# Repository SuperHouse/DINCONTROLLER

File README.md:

DIN-Mount ESP32 Controller with I/O Breakout
=============================================
Copyright 2017-2018 SuperHouse Automation Pty Ltd  www.superhouse.tv  

ESP32 controller board designed to fit into the top part of DIN rail
case H8456.

Includes 8 illuminated buttons for input, and an I/O Breakout header
(12-pin IDC) compatible with other I/O Breakout boards from SuperHouse.

More information is available at:

  http://www.superhouse.tv/dinrelay8

INSTALLATION
------------
The design is saved as an EAGLE project. EAGLE PCB design software is
available from www.cadsoftusa.com free for non-commercial use. To use
this project download it and place the directory containing these files
into the "eagle" directory on your computer. Then open EAGLE and
navigate to the project.

DISTRIBUTION
------------
The specific terms of distribution of this project are governed by the
license referenced below.

LICENSE
-------
Licensed under the TAPR Open Hardware License (www.tapr.org/OHL).
The "license" folder within this repository also contains a copy of
this license in plain text format.

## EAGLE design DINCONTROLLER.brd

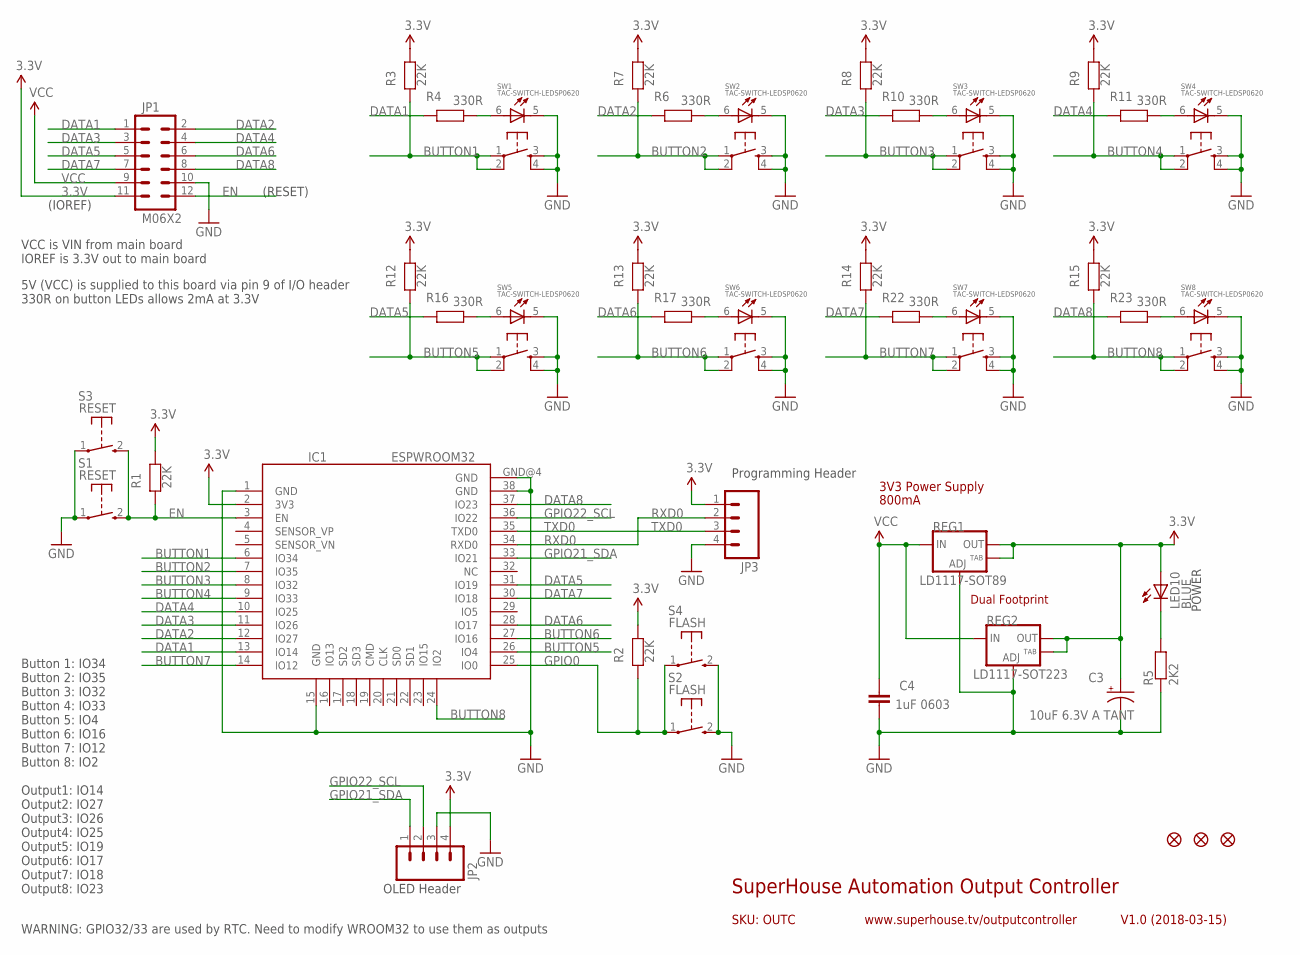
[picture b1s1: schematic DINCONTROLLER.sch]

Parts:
C3: 10uF 6.3V A TANT; EIA3216
C4: 1uF 0603; 0603
FID1, FID2, FID3: FIDUCIAL1X2.5; FIDUCIAL-1X2.5
IC1: ESPWROOM32
JP1: M06X2; 2X6-SHROUDED
JP2, JP3: M04PTH; 1X04
LED10: BLUE; LED3MM
R1, R2, R3, R7, R8, R9, R12, R13, R14, R15: 22K; 0603@2
R4, R6, R10, R11, R16, R17, R22, R23: 330R; 0603@2
R5: 2K2; 0603
REG1: LD1117-SOT89; SOT89
REG2: LD1117-SOT223; SOT223
S1, S3: RESET; TACTILE_SWITCH_SMD_2PIN_TINY
S2, S4: FLASH; TACTILE_SWITCH_SMD_2PIN_TINY
SW1, SW2, SW3, SW4, SW5, SW6, SW7, SW8: TAC-SWITCH-LEDSP0620; TACTILE-PTH-SP0620

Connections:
3.3V: C3.A (+), IC1.2 (3V3), JP1.11, JP2.4, JP3.1, LED10.A, R1.1, R2.1, R3.1, R7.1, R8.1, R9.1, R12.1, R13.1, R14.1, R15.1, REG1.2 (OUT), REG1.4 (OUT), REG2.2 (OUT), REG2.4 (OUT)
BUTTON1: IC1.6 (IO34), R3.2, SW1.1, SW1.2 (6)
BUTTON2: IC1.7 (IO35), R7.2, SW2.1, SW2.2 (6)
BUTTON3: IC1.8 (IO32), R8.2, SW3.1, SW3.2 (6)
BUTTON4: IC1.9 (IO33), R9.2, SW4.1, SW4.2 (6)
BUTTON5: IC1.26 (IO4), R12.2, SW5.1, SW5.2 (6)
BUTTON6: IC1.27 (IO16), R13.2, SW6.1, SW6.2 (6)
BUTTON7: IC1.14 (IO12), R14.2, SW7.1, SW7.2 (6)
BUTTON8: IC1.24 (IO2), R15.2, SW8.1, SW8.2 (6)
DATA1: IC1.13 (IO14), JP1.1, R4.2
DATA2: IC1.12 (IO27), JP1.2, R6.2
DATA3: IC1.11 (IO26), JP1.3, R10.2
DATA4: IC1.10 (IO25), JP1.4, R11.2
DATA5: IC1.31 (IO19), JP1.5, R16.2
DATA6: IC1.28 (IO17), JP1.6, R17.2
DATA7: IC1.30 (IO18), JP1.7, R22.2
DATA8: IC1.37 (IO23), JP1.8, R23.2
EN: IC1.3 (EN), JP1.12, R1.2, S1.2 (S), S3.2 (S)
GND: C3.C (-), C4.2, IC1.1 (GND), IC1.15 (GND), IC1.38 (GND), IC1.GND@4 (GND), JP1.10, JP2.3, JP3.4, R5.1, REG1.1 (ADJ), REG2.1 (ADJ), S1.1, S2.2 (S), S3.1, S4.2 (S), SW1.3, SW1.4, SW1.5 (C), SW2.3, SW2.4, SW2.5 (C), SW3.3, SW3.4, SW3.5 (C), SW4.3, SW4.4, SW4.5 (C), SW5.3, SW5.4, SW5.5 (C), SW6.3, SW6.4, SW6.5 (C), SW7.3, SW7.4, SW7.5 (C), SW8.3, SW8.4, SW8.5 (C)
GPIO0: IC1.25 (IO0), R2.2, S2.1, S4.1
GPIO21_SDA: IC1.33 (IO21), JP2.1
GPIO22_SCL: IC1.36 (IO22), JP2.2
unnamed: R4.1, SW1.6 (A)
unnamed: R11.1, SW4.6 (A)
unnamed: R6.1, SW2.6 (A)
unnamed: R10.1, SW3.6 (A)
unnamed: LED10.K (C), R5.2
unnamed: R16.1, SW5.6 (A)
unnamed: R17.1, SW6.6 (A)
unnamed: R22.1, SW7.6 (A)
unnamed: R23.1, SW8.6 (A)
RXD0: IC1.34 (RXD0), JP3.2
TXD0: IC1.35 (TXD0), JP3.3
VCC: C4.1, JP1.9, REG1.3 (IN), REG2.3 (IN)

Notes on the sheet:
SKU: OUTC
SuperHouse Automation Output Controller
V1.0 (2018-03-15)
www.superhouse.tv/outputcontroller
Button 1: IO34 Button 2: IO35 Button 3: IO32 Button 4: IO33 Button 5: IO4 Button 6: IO16 Button 7: IO12 Button 8: IO2 Output1: IO14 Output2: IO27 Output3: IO26 Output4: IO25 Output5: IO19 Output6: IO17 Output7: IO18 Output8: IO23
VCC is VIN from main board IOREF is 3.3V out to main board
5V (VCC) is supplied to this board via pin 9 of I/O header 330R on button LEDs allows 2mA at 3.3V
POWER
3V3 Power Supply
Dual Footprint
800mA
(IOREF)
WARNING: GPIO32/33 are used by RTC. Need to modify WROOM32 to use them as outputs
OLED Header
Programming Header
(RESET)

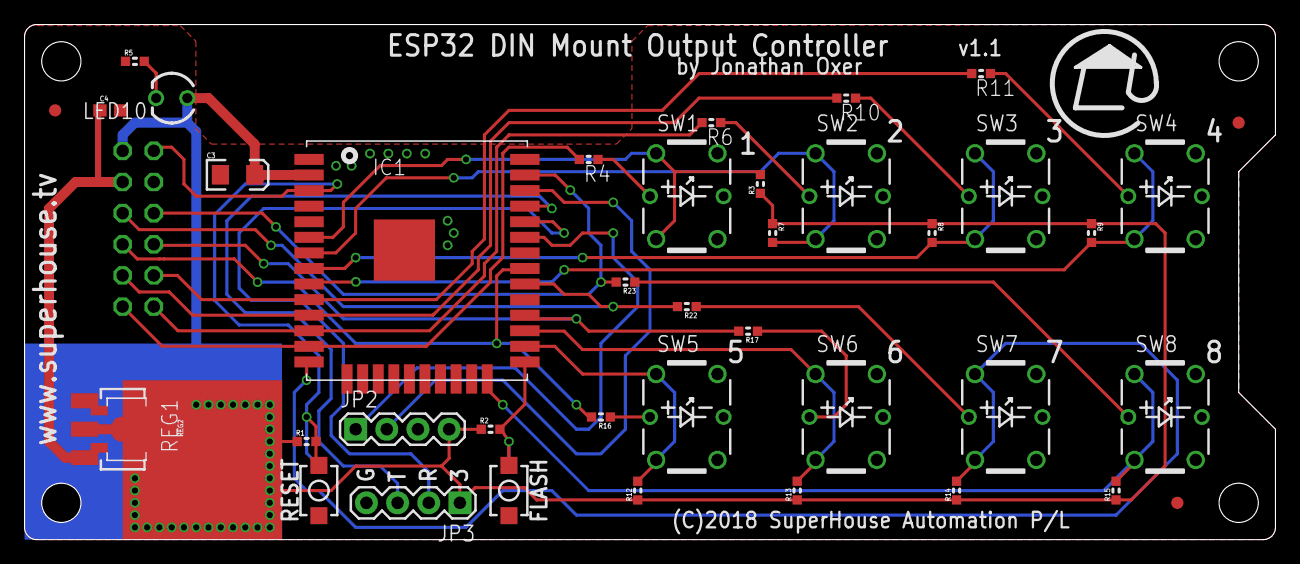
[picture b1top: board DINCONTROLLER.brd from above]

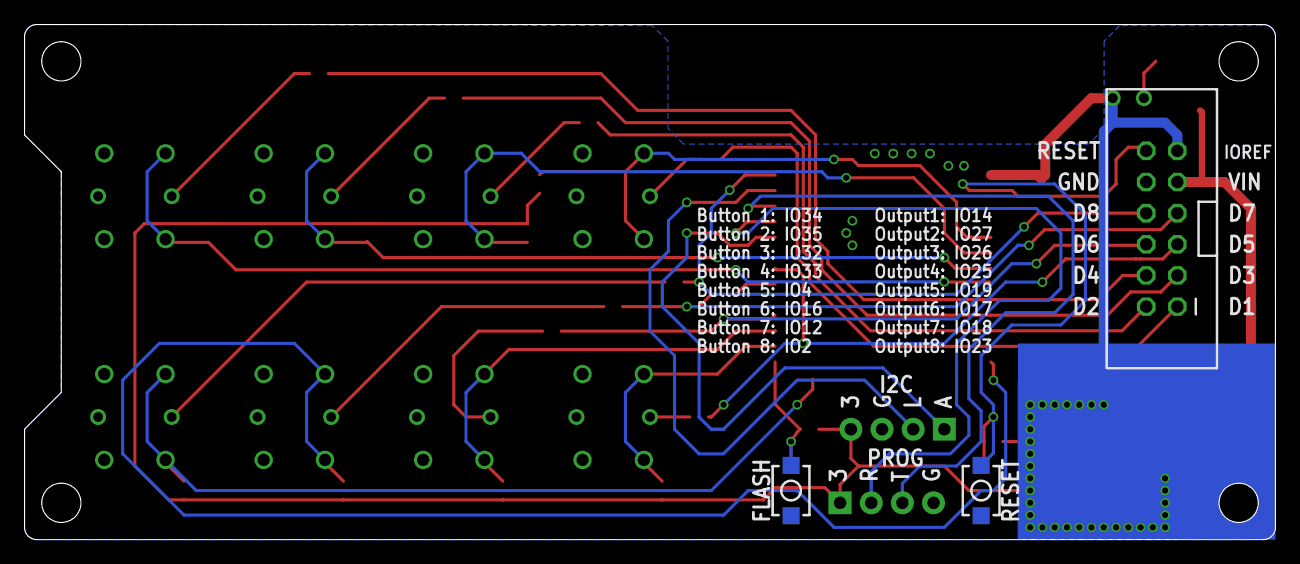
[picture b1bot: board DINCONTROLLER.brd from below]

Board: 2 copper layers, 102.0 x 42.0 mm, 43 parts (3 on the bottom side), 34 nets.

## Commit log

2018-03-28 Initial project import
2018-04-10 Improved designators
2018-04-22 Updated notes for v1.0 release
2018-04-23 Major update: remapped IO pins for v1.1 release
2019-04-23 Improved designator visibility

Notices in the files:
DINCONTROLLER.brd:
(C)2018 SuperHouse Automation P/L
parts and their libraries:
freetronics-original: Licensing: CC v3.0 Share-Alike You are welcome to use this library for commercial purposes.
